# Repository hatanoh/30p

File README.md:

## はじめに
本品は試作品です。

キーボードとしての基本的な動作には問題がないことは確認していますが、多少ネジ穴位置や組み立て難易度に難があります。

その辺りご了承ください。

## どんなキーボード
BLE Micro Proを使用する31～35キーで3段の細長いキーボードで単3電池1本で駆動します。

トッププレート裏にBMPを配置しているのでProMicroを重ねないタイプの普通のキーボードぐらいの厚さ(7mmスペーサー使用)になっています
(Bootleg31除く/Bootleg31は11mm)

### Bootleg31
Nomu30の配列でBMP対応して、レバースイッチを付けたキーボード。
レバースイッチは親指で操作してレイヤ切り替えなどに使うことを想定しています。

### Soroban30(Bootleg30)
40%キーボードの最下段をちょん切って、「,」「.」のスペースの2uスペースを置いたキーボード

スペースを小指で叩くちょっと苦しいキーボード

### Ally13(黒)
soroban30を13°づつ折り曲げて隙間にスイッチを一つ入れたもの

Ally24の中央のBSがない配列になります

### Ally24(赤)

soroban30を24°づつ折り曲げて隙間にスイッチを二つ入れたもの

キー配置の詳細はソースのkeymap.cを参照してください

## ビルドガイド
[Build Guide](https://github.com/hatanoh/30p/blob/master/Doc/buildguide.md)

## ファームウェア
[Firmware/BLE Micro Pro](https://github.com/hatanoh/qmk_firmware)

[キーボード固有部分](https://github.com/hatanoh/qmk_firmware/tree/nrf52/keyboards/sarasarado30_ble)

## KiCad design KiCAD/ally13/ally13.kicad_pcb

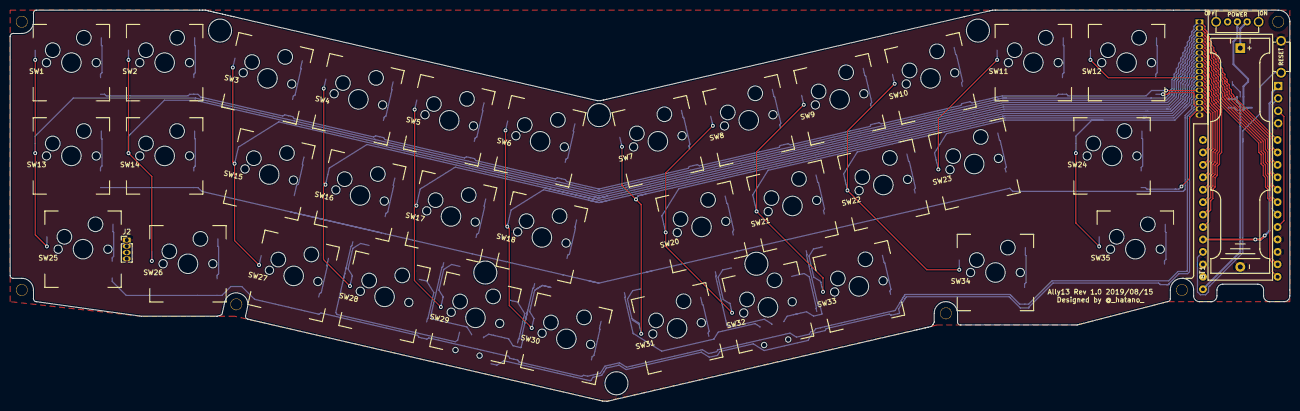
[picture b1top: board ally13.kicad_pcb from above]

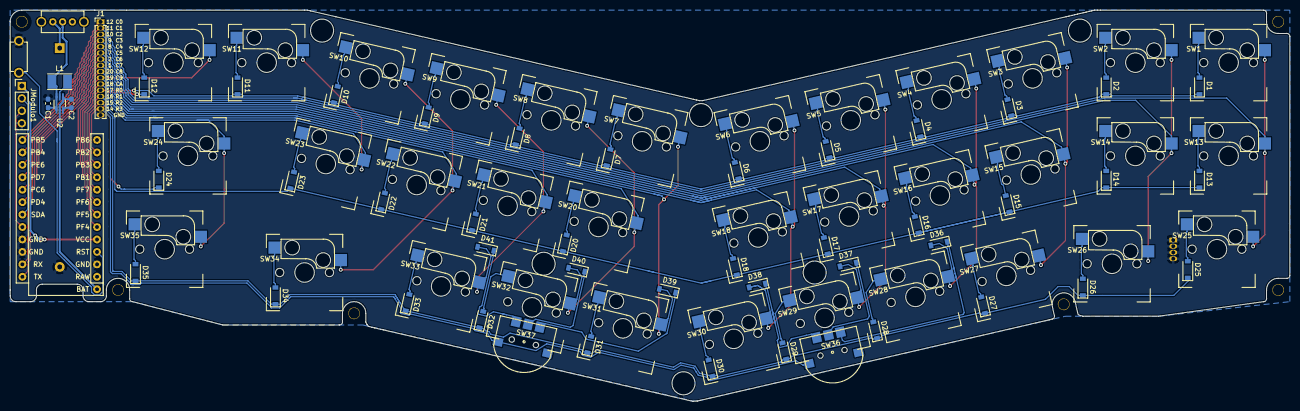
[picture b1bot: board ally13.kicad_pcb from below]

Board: 2 copper layers, 261.3 x 79.9 mm, 99 parts (50 on the bottom side), 64 nets.

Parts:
BT1: Battery_Cell; BatteryHolder_Keystone_2466_1xAAA
C1, C2: 10uF; C_0603_1608Metric_Pad1.05x0.95mm_HandSolder
D1, D2, D3, D4, D5, D6, D7, D8, D9, D10, D11, D12, D13, D14, D15, D16, D17, D18, D20, D21, D22, D23, D24, D25, D26, D27, D28, D29, D30, D31, D32, D33, D34, D35, D36, D37, D38, D39, D40, D41: D; D_SOD-123
H1, H2, H4, H5, H6, H10: MountingHole; HOLE_M2_TH
H3, H7, H8, H9, H11, H12: MountingHole; HOLE_M2
J1: Conn_01x16; PinHeader_1x16_P1.27mm_Conthrough
J2: Conn_01x04; PinHeader_1x04_P1.27mm_Conthrough
JModulo1: Conn_01x04; PinHeader_1x04_P2.54mm_Vertical
L1: 4.7uH; L_Taiyo-Yuden_NR-30xx_HandSoldering
SW1, SW2, SW3, SW4, SW5, SW6, SW7, SW8, SW9, SW10, SW11, SW12, SW13, SW14, SW15, SW16, SW17, SW18, SW20, SW21, SW22, SW23, SW26, SW27, SW28, SW29, SW30, SW31, SW32, SW33: SW_Push; CPG1511_1u
SW24, SW34: SW_Push; CPG1511_1.75u
SW25, SW35: SW_Push; CPG1511_1.25u
SW36, SW37: TMHU27; THMU27
SW38: SW_RST; TACT_SWITCH_TVBP06
SW39: SW_PWR; SLIDE_SWITCH_SK-12D01
U1: BLE-Micro-Pro-2; BLEMicroPro-2N
U2: TPS61221; SOT-363_SC-70-6_Handsoldering

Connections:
BAT: C2.1, U1.25, U2.2, U2.4
C0: J1.1, SW1.1, SW13.1, SW25.1, U1.12
C1: J1.2, SW2.1, SW14.1, SW26.1, U1.11
C2: J1.3, SW3.1, SW15.1, SW27.1, U1.10
C3: D36.2, J1.4, SW4.1, SW16.1, SW28.1, U1.9
C4: D37.2, J1.5, SW5.1, SW17.1, SW29.1, U1.8
C5: D38.2, J1.6, SW6.1, SW18.1, SW30.1, U1.7
C6: D39.2, J1.7, SW7.1, SW31.1, U1.2
C7: D40.2, J1.8, SW8.1, SW20.1, SW32.1, U1.1
C8: D41.2, J1.9, SW9.1, SW21.1, SW33.1, U1.20
C9: J1.10, SW10.1, SW12.1, SW22.1, SW34.1, U1.19
C10: J1.11, SW11.1, SW23.1, SW24.1, SW35.1, U1.18
GND: BT1.2, C1.2, C2.2, J1.16, J2.1, J2.2, J2.3, J2.4, JModulo1.4, SW38.2, U1.3, U1.4, U1.23, U2.3
unnamed: BT1.1, SW39.2
unnamed: D1.2, SW1.2
unnamed: D2.2, SW2.2
unnamed: D3.2, SW3.2
unnamed: D4.2, SW4.2
unnamed: D5.2, SW5.2
unnamed: D6.2, SW6.2
unnamed: D7.2, SW7.2
unnamed: D8.2, SW8.2
unnamed: D9.2, SW9.2
unnamed: D10.2, SW10.2
unnamed: D11.2, SW11.2
unnamed: D12.2, SW12.2
unnamed: D13.2, SW13.2
unnamed: D14.2, SW14.2
unnamed: D15.2, SW15.2
unnamed: D16.2, SW16.2
unnamed: D17.2, SW17.2
unnamed: D18.2, SW18.2
unnamed: D20.2, SW20.2
unnamed: D21.2, SW21.2
unnamed: D22.2, SW22.2
unnamed: D23.2, SW23.2
unnamed: D24.2, SW24.2
unnamed: D25.2, SW25.2
unnamed: D26.2, SW26.2
unnamed: D27.2, SW27.2
unnamed: D28.2, SW28.2
unnamed: D29.2, SW29.2
unnamed: D30.2, SW30.2
unnamed: D31.2, SW31.2
unnamed: D32.2, SW32.2
unnamed: D33.2, SW33.2
unnamed: D34.2, SW34.2
unnamed: D35.2, SW35.2
unnamed: D36.1, SW36.1
unnamed: D37.1, SW36.T
unnamed: D38.1, SW36.2
unnamed: D39.1, SW37.1
unnamed: D40.1, SW37.T
unnamed: D41.1, SW37.2
unnamed: L1.1, U2.5
R0: D1.1, D2.1, D3.1, D4.1, D5.1, D6.1, D7.1, D8.1, D9.1, D10.1, D11.1, J1.12, U1.17
R1: D13.1, D14.1, D15.1, D16.1, D17.1, D18.1, D20.1, D21.1, D22.1, D23.1, J1.13, U1.16
R2: D25.1, D26.1, D27.1, D28.1, D29.1, D30.1, D31.1, D32.1, D33.1, D34.1, D35.1, J1.14, U1.15
R3: D12.1, D24.1, J1.15, SW36.C, SW37.C, U1.14
RST: SW38.1, U1.22
SCL: JModulo1.3, U1.5
SDA: JModulo1.2, U1.6
VCC: JModulo1.1, U1.21
cell: C1.1, L1.2, SW39.1, U2.1, U2.6

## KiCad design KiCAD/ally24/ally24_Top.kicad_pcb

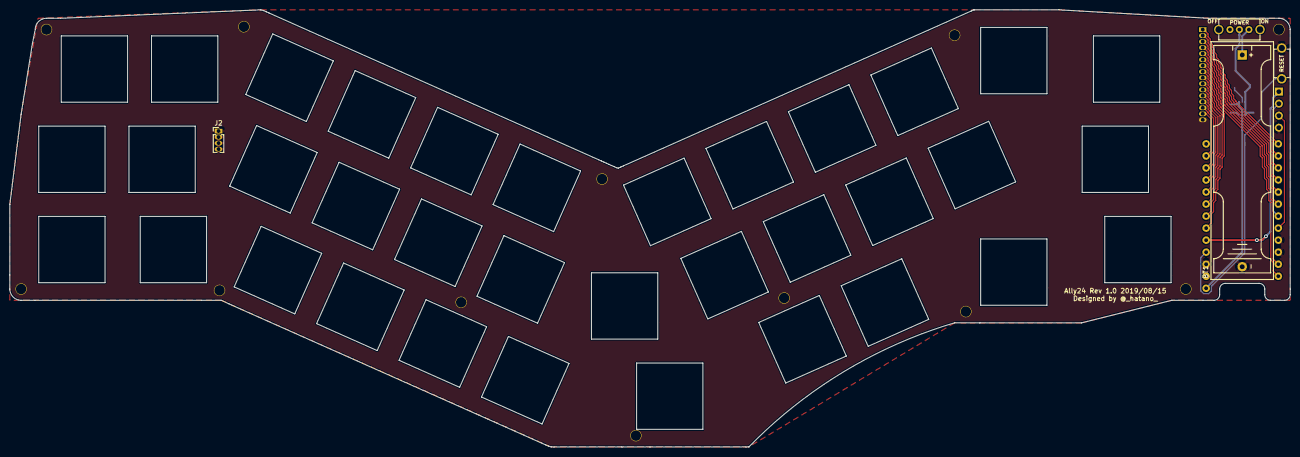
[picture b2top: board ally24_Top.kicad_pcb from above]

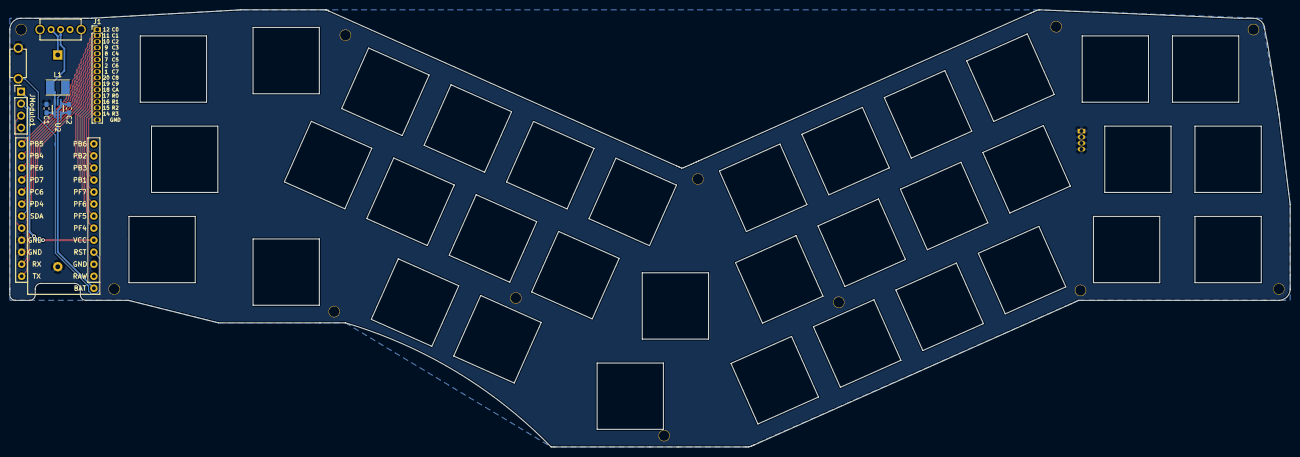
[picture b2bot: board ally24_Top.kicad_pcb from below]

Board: 2 copper layers, 270.3 x 92.3 mm, 58 parts (8 on the bottom side), 24 nets.

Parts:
BT1: Battery_Cell; BatteryHolder_Keystone_2466_1xAAA
C1, C2: 10uF; C_0603_1608Metric_Pad1.05x0.95mm_HandSolder
H1, H2, H3, H4, H5, H6, H7, H8, H9, H10, H11, H12: MountingHole; HOLE_M2
J1: Conn_01x16; PinHeader_1x16_P1.27mm_Conthrough
J2: Conn_01x04; PinHeader_1x04_P1.27mm_Conthrough
JModulo1: Conn_01x04; PinHeader_1x04_P2.54mm_Vertical
L1: 4.7uH; L_Taiyo-Yuden_NR-30xx_HandSoldering
SW1, SW2, SW3, SW4, SW5, SW6, SW7, SW8, SW9, SW10, SW11, SW12, SW13, SW14, SW15, SW16, SW17, SW18, SW19, SW20, SW21, SW22, SW23, SW24, SW25, SW26, SW27, SW28, SW29, SW30, SW31, SW32, SW33, SW34, SW35: SW_Push; CPG1511_1350_hole
SW38: SW_RST; TACT_SWITCH_TVBP06
SW39: SW_PWR; SLIDE_SWITCH_SK-12D01
U1: BLE-Micro-Pro-2; BLEMicroPro-2N
U2: TPS61221; SOT-363_SC-70-6_Handsoldering

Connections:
BAT: C2.1, U1.25, U2.2, U2.4
C0: J1.1, U1.12
C1: J1.2, U1.11
C2: J1.3, U1.10
C3: J1.4, U1.9
C4: J1.5, U1.8
C5: J1.6, U1.7
C6: J1.7, U1.2
C7: J1.8, U1.1
C8: J1.9, U1.20
C9: J1.10, U1.19
C10: J1.11, U1.18
GND: BT1.2, C1.2, C2.2, J1.16, J2.1, J2.2, J2.3, J2.4, JModulo1.4, SW38.2, U1.3, U1.4, U1.23, U2.3
unnamed: BT1.1, SW39.2
unnamed: L1.1, U2.5
R0: J1.12, U1.17
R1: J1.13, U1.16
R2: J1.14, U1.15
R3: J1.15, U1.14
RST: SW38.1, U1.22
SCL: JModulo1.3, U1.5
SDA: JModulo1.2, U1.6
VCC: JModulo1.1, U1.21
cell: C1.1, L1.2, SW39.1, U2.1, U2.6

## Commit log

2019-08-29 add new 30$ keyboards
